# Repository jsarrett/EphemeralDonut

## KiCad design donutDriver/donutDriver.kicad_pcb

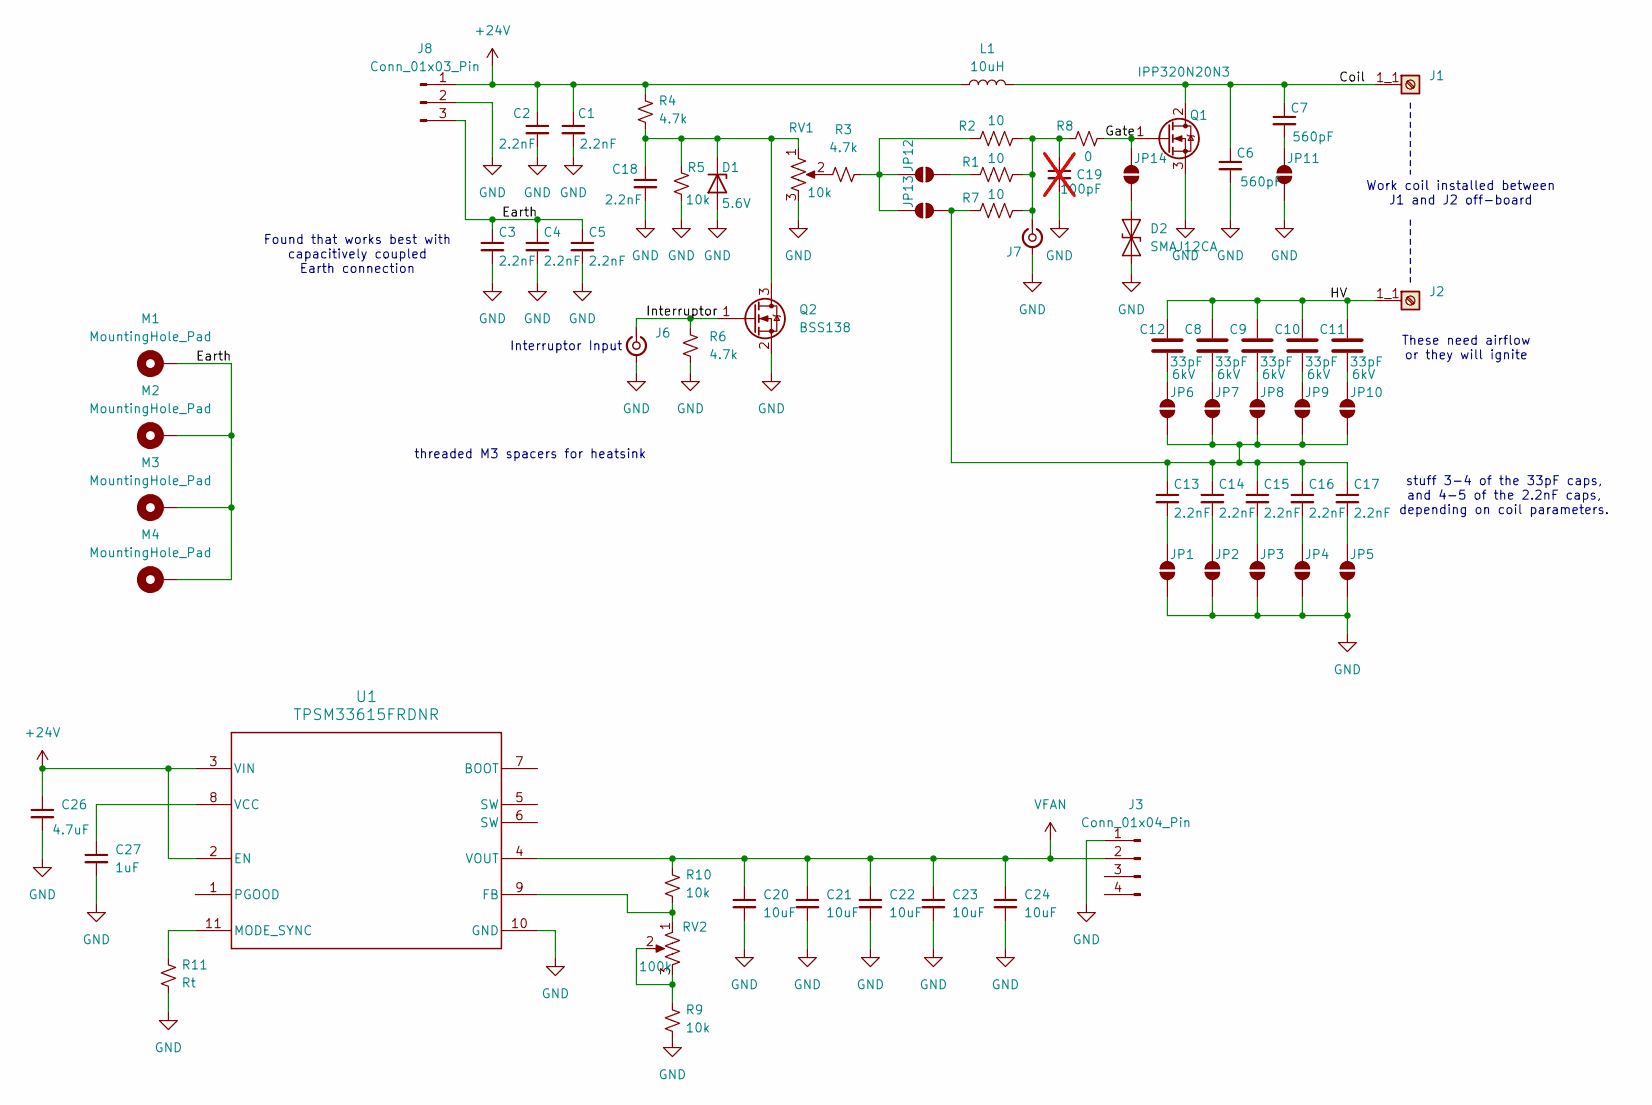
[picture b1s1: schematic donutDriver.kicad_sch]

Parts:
C1, C2, C3, C4, C5, C13, C14, C15, C16, C17, C18: 2.2nF; C_0805_2012Metric; Voltage 250V; MPN C0805C222JAGACAUTO
C6, C7: 560pF; C_1206_3216Metric; MPN CC1206JRNPOBBN561
C8, C9, C10, C11, C12: 33pF; TDK_Disc_D7.5mm_W5.0mm_P7.50mm; Voltage 6kV; MPN CC45SL3JD330JYNNA
C19: 100pF; C_1206_3216Metric; not fitted
C20, C21, C22, C23, C24: 10uF; C_0805_2012Metric
C26: 4.7uF; C_1210_3225Metric
C27: 1uF; C_0603_1608Metric
D1: 5.6V; D_SOD-323_HandSoldering; MPN CUHZ5V6.H3F
D2: SMAJ12CA; D_SMA
J1, J2: Keystone 7767; KEYSTONE_7767
J3: Conn_01x04_Pin; JST_XH_B4B-XH-A_1x04_P2.50mm_Vertical
J6, J7: Conn_Coaxial_Small; SMA_Amphenol_132134-11_Vertical
J8: Conn_01x03_Pin; CONN3_2601-3103_WAG
JP1, JP2, JP3, JP4, JP5, JP6, JP7, JP8, JP9, JP10, JP11, JP12, JP13, JP14: SolderJumper_2_Open; SolderJumper-2_P1.3mm_Open_RoundedPad1.0x1.5mm
L1: 10uH; L_Toroid_Vertical_L16.3mm_W7.1mm_P7.11mm_Pulse_H
M1, M2, M3, M4: MountingHole_Pad; WA-SMSI_9774025360
Q1: IPP320N20N3; TO-220-3_Horizontal_BoardCutout
Q2: BSS138; SOT-23
R1, R2, R7: 10; R_2512_6332Metric; MPN SR2512JK-7W10RL
R3, R4, R6: 4.7k; R_0603_1608Metric
R5, R9, R10: 10k; R_0603_1608Metric
R8: 0; R_1206_3216Metric
R11: Rt; R_0603_1608Metric
RV1: 10k; Potentiometer_Bourns_PTV09A-2_Single_Horizontal; MPN PTV09A-2025F-B103
RV2: 100k; Potentiometer_Bourns_PTV09A-2_Single_Horizontal; MPN PTV09A-2025F-B104
U1: TPSM33615FRDNR; RDN0011A-MFG

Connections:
+24V: C1.1, C2.1, C26.1, J8.1, L1.1, R4.2, U1.2 (EN), U1.3 (VIN)
/Coil: C6.1, C7.1, J1.1_1 (Pin_1), J1.1_2 (Pin_1), J1.1_3 (Pin_1), J1.1_4 (Pin_1), L1.2, Q1.2 (D)
/Earth: C3.1, C4.1, C5.1, J8.3, M1.1, M2.1, M3.1, M4.1
/Gate: JP14.2 (B), Q1.1 (G), R8.2
/HV: C8.1, C9.1, C10.1, C11.1, C12.1, J2.1_1 (Pin_1), J2.1_2 (Pin_1), J2.1_3 (Pin_1), J2.1_4 (Pin_1)
/Interruptor: J6.1 (In), Q2.1 (G), R6.2
GND: C1.2, C2.2, C3.2, C4.2, C5.2, C6.2, C18.2, C19.2, C20.2, C21.2, C22.2, C23.2, C24.2, C26.2, C27.2, D1.2 (A), D2.1 (A1), J3.1, J6.2 (Ext), J7.2 (Ext), J8.2, JP1.1 (A), JP2.1 (A), JP3.1 (A), JP4.1 (A), JP5.1 (A), JP11.1 (A), Q1.3 (S), Q2.2 (S), R5.1, R6.1, R9.1, R11.1, RV1.3, U1.10 (GND)
unnamed: C18.1, D1.1 (K), Q2.3 (D), R4.1, R5.2, RV1.1
unnamed: D2.2 (A2), JP14.1 (A)
unnamed: C19.1, J7.1 (In), R1.2, R2.2, R7.2, R8.1
unnamed: C13.2, JP1.2 (B)
unnamed: C14.2, JP2.2 (B)
unnamed: C15.2, JP3.2 (B)
unnamed: C16.2, JP4.2 (B)
unnamed: C17.2, JP5.2 (B)
unnamed: C12.2, JP6.2 (B)
unnamed: C8.2, JP7.2 (B)
unnamed: C9.2, JP8.2 (B)
unnamed: C10.2, JP9.2 (B)
unnamed: C13.1, C14.1, C15.1, C16.1, C17.1, JP6.1 (A), JP7.1 (A), JP8.1 (A), JP9.1 (A), JP10.1 (A), JP13.1 (A), R7.1
unnamed: C11.2, JP10.2 (B)
unnamed: C7.2, JP11.2 (B)
unnamed: JP12.1 (A), R1.1
unnamed: JP12.2 (B), JP13.2 (B), R2.1, R3.2
unnamed: R3.1, RV1.2
unnamed: R9.2, RV2.2, RV2.3
unnamed: R10.1, RV2.1, U1.9 (FB)
unnamed: R11.2, U1.11 (MODE_SYNC)
unnamed: C27.1, U1.8 (VCC)
VFAN: C20.1, C21.1, C22.1, C23.1, C24.1, J3.2, R10.2, U1.4 (VOUT)

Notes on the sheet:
Work coil installed between J1 and J2 off-board
Interruptor Input
threaded M3 spacers for heatsink
These need airflow or they will ignite
stuff 3-4 of the 33pF caps, and 4-5 of the 2.2nF caps, depending on coil parameters.
Found that works best with capacitively coupled Earth connection

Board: 2 copper layers, 69 parts (0 on the bottom side), 30 nets, no tracks yet.

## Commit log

2024-10-21 Add CC-BY-NC-SA 4.0 License
2024-11-11 begin basic class E implementation
    schematic matches my handmade prototypes pretty closely
2024-11-12 begin pcb
2024-11-14 add fan switching regulator and jumpers
